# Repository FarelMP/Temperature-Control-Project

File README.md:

# Temperature-Control-Project
This is the result of the assignment of the interface and microcontroller workshop course, the project aims to measure voltage, current and tempereture while controlling brightness of halogen lamp. After all measruements, the data will visualize through node red using serial communication.

Contain included:
- Schematic and PCB layout (EAGLE).
- Node red JSON source file.
- STM32G431RBTX program for sensor reading and measurement.

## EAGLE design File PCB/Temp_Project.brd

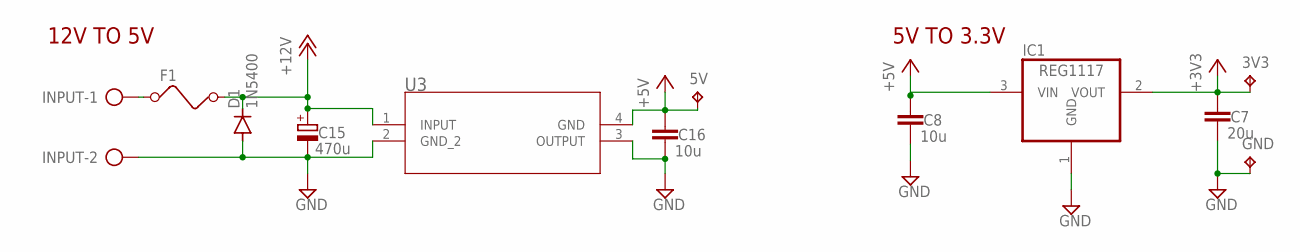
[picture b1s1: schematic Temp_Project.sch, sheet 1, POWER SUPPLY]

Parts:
3V3, 5V: TPPAD1-13; P1-13
C7: 20u; C0805
C8, C16: 10u; C0805
C15: 470u; E5-10,5
D1: 1N5400; DO201-15
F1: FUSE
GND: TPPAD1-13; P1-13
IC1: REG1117; SOT223
INPUT: AK500/2-H
U3: LM7805MPX/NOPBDCY4_TEX; DCY4_TEX

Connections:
+3V3: 3V3.TP, C7.1, IC1.2 (VOUT); also elsewhere on the board
+5V: 5V.TP, C8.1, C16.1, IC1.3 (VIN), U3.4 (GND); also elsewhere on the board
+12V: C15.+, D1.C, F1.2, U3.1 (INPUT); also elsewhere on the board
GND: C7.2, C8.2, C15.-, C16.2, D1.A, GND.TP, IC1.1 (GND), INPUT.2, U3.2 (GND_2), U3.3 (OUTPUT); also elsewhere on the board
unnamed: F1.1, INPUT.1

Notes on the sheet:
12V TO 5V
5V TO 3.3V

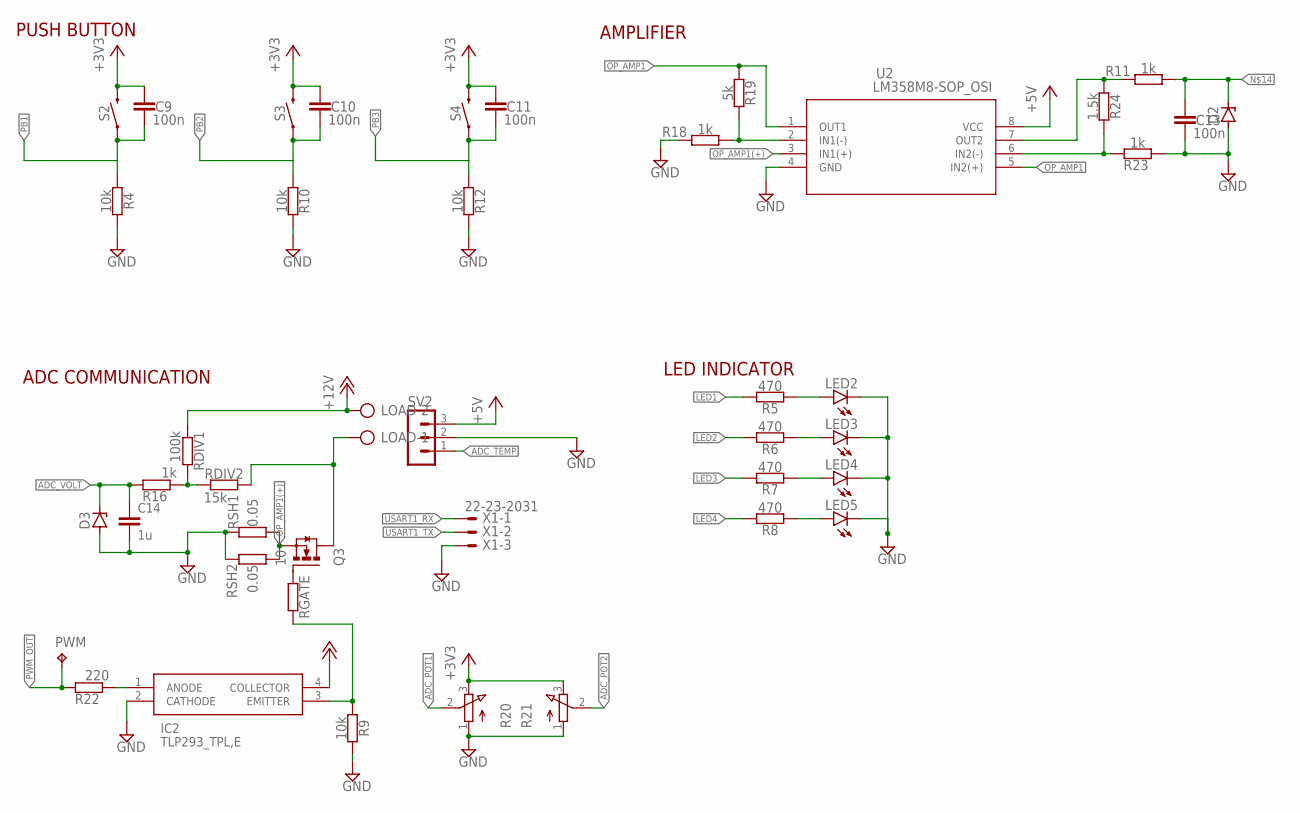
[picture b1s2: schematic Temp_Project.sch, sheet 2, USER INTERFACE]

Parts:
C9, C10, C11, C13: 100n; C0805
C14: 1u; C0805
D2, D3: ZENER 3V3; SOD80C
IC2: TLP293_TPL,E; SOIC127P700X220-4N
LED2, LED3, LED4, LED5: LED3MM
LOAD: AK500/2-H
PWM: TPPAD1-13; P1-13
Q3: IRFZ44N; SOT223
R4, R9, R10, R12: 10k; R0805
R5, R6, R7, R8: 470; R0805
R11, R16, R18, R23: 1k; R0805
R19: 5k; R0805
R20, R21: 3RP/1610N
R22: 220; R0805
R24: 1.5k; R0805
RDIV1: 100k; R0805
RDIV2: 15k; R0805
RGATE: 10; R0805
RSH1, RSH2: 0.05; 0617/22
S2, S3, S4: MOMENTARY-SWITCH-SPST-SMD-6.0X3.5MM; TACTILE_SWITCH_SMD_6.0X3.5MM
SV2: MA03-1
U2: LM358M8-SOP_OSI; 8-SOP_OSI
X1: 22-23-2031

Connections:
+3V3: C9.1, C10.1, C11.1, R20.3 (E), R21.3 (E), S2.2, S3.2, S4.2; also elsewhere on the board
+5V: SV2.3, U2.8 (VCC); also elsewhere on the board
+12V: IC2.4 (COLLECTOR), LOAD.2, RDIV1.1; also elsewhere on the board
ADC_CUR: R11.2, R24.1, U2.7 (OUT2); also elsewhere on the board
ADC_POT1: R20.2 (S); also elsewhere on the board
ADC_POT2: R21.2 (S); also elsewhere on the board
ADC_TEMP: SV2.1; also elsewhere on the board
ADC_VOLT: C14.1, D3.C, R16.2; also elsewhere on the board
GND: C13.2, C14.2, D2.A, D3.A, IC2.2 (CATHODE), LED2.K (C), LED3.K (C), LED4.K (C), LED5.K (C), R4.1, R9.1, R10.1, R12.1, R18.2, R20.1 (A), R21.1 (A), R23.1, RSH1.1, RSH2.1, SV2.2, U2.4 (GND), X1.3; also elsewhere on the board
LED1: R5.1; also elsewhere on the board
LED2: R6.1; also elsewhere on the board
LED3: R7.1; also elsewhere on the board
LED4: R8.1; also elsewhere on the board
unnamed: LED2.A, R5.2
unnamed: LED3.A, R6.2
unnamed: LED4.A, R7.2
unnamed: LED5.A, R8.2
unnamed: IC2.1 (ANODE), R22.1
unnamed: Q3.1 (G), RGATE.1
unnamed: LOAD.1, Q3.2 (D), Q3.4 (D), RDIV2.2
unnamed: IC2.3 (EMITTER), R9.2, RGATE.2
unnamed: C13.1, D2.C, R11.1
unnamed: R18.1, R19.1, U2.2 (IN1(-))
unnamed: R16.1, RDIV1.2, RDIV2.1
unnamed: R23.2, R24.2, U2.6 (IN2(-))
OP_AMP1: R19.2, U2.1 (OUT1), U2.5 (IN2(+))
OP_AMP1(+): Q3.3 (S), RSH1.2, RSH2.2, U2.3 (IN1(+))
PB1: C9.2, R4.2, S2.1; also elsewhere on the board
PB2: C10.2, R10.2, S3.1; also elsewhere on the board
PB3: C11.2, R12.2, S4.1; also elsewhere on the board
PWM_OUT: PWM.TP, R22.2; also elsewhere on the board
USART1_RX: X1.1; also elsewhere on the board
USART1_TX: X1.2; also elsewhere on the board

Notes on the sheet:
PUSH BUTTON
AMPLIFIER
ADC COMMUNICATION
LED INDICATOR

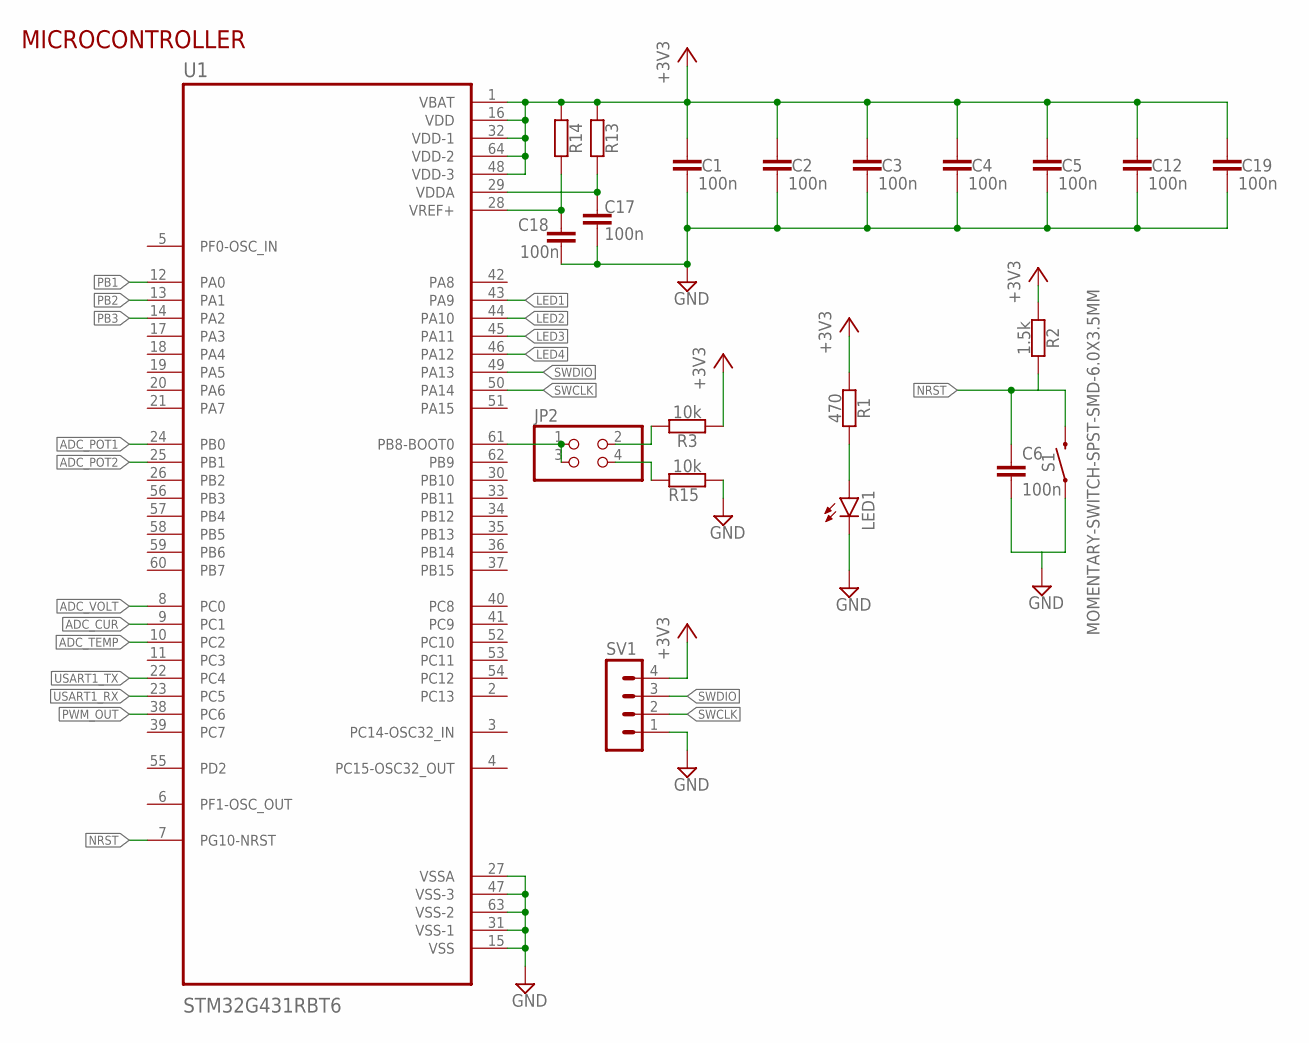
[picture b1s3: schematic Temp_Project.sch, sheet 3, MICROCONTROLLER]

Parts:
C1, C2, C3, C4, C5, C6, C12, C17, C18, C19: 100n; C0805
JP2: PINHD-2X2; 2X02
LED1: LEDCHIPLED_0805; CHIPLED_0805
R1: 470; R0805
R2: 1.5k; R0805
R3, R15: 10k; R0805
R13, R14: R-EU_R0603; R0603
S1: MOMENTARY-SWITCH-SPST-SMD-6.0X3.5MM; TACTILE_SWITCH_SMD_6.0X3.5MM
SV1: MA04-1
U1: STM32G431RBT6; QFP50P1200X1200X160-64N

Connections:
+3V3: C1.1, C2.1, C3.1, C4.1, C5.1, C12.1, C19.1, R1.1, R2.1, R3.1, R13.2, R14.2, SV1.4, U1.1 (VBAT), U1.16 (VDD), U1.32 (VDD-1), U1.48 (VDD-3), U1.64 (VDD-2); also elsewhere on the board
ADC_CUR: U1.9 (PC1); also elsewhere on the board
ADC_POT1: U1.24 (PB0); also elsewhere on the board
ADC_POT2: U1.25 (PB1); also elsewhere on the board
ADC_TEMP: U1.10 (PC2); also elsewhere on the board
ADC_VOLT: U1.8 (PC0); also elsewhere on the board
GND: C1.2, C2.2, C3.2, C4.2, C5.2, C6.2, C12.2, C17.2, C18.2, C19.2, LED1.C, R15.2, S1.1, SV1.1, U1.15 (VSS), U1.27 (VSSA), U1.31 (VSS-1), U1.47 (VSS-3), U1.63 (VSS-2); also elsewhere on the board
LED1: U1.43 (PA9); also elsewhere on the board
LED2: U1.44 (PA10); also elsewhere on the board
LED3: U1.45 (PA11); also elsewhere on the board
LED4: U1.46 (PA12); also elsewhere on the board
unnamed: LED1.A, R1.2
unnamed: JP2.1, JP2.3, U1.61 (PB8-BOOT0)
unnamed: JP2.2, R3.2
unnamed: JP2.4, R15.1
unnamed: C17.1, R13.1, U1.29 (VDDA)
unnamed: C18.1, R14.1, U1.28 (VREF+)
NRST: C6.1, R2.2, S1.2, U1.7 (PG10-NRST)
PB1: U1.12 (PA0); also elsewhere on the board
PB2: U1.13 (PA1); also elsewhere on the board
PB3: U1.14 (PA2); also elsewhere on the board
PWM_OUT: U1.38 (PC6); also elsewhere on the board
SWCLK: SV1.2, U1.50 (PA14)
SWDIO: SV1.3, U1.49 (PA13)
USART1_RX: U1.23 (PC5); also elsewhere on the board
USART1_TX: U1.22 (PC4); also elsewhere on the board

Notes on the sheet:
MICROCONTROLLER

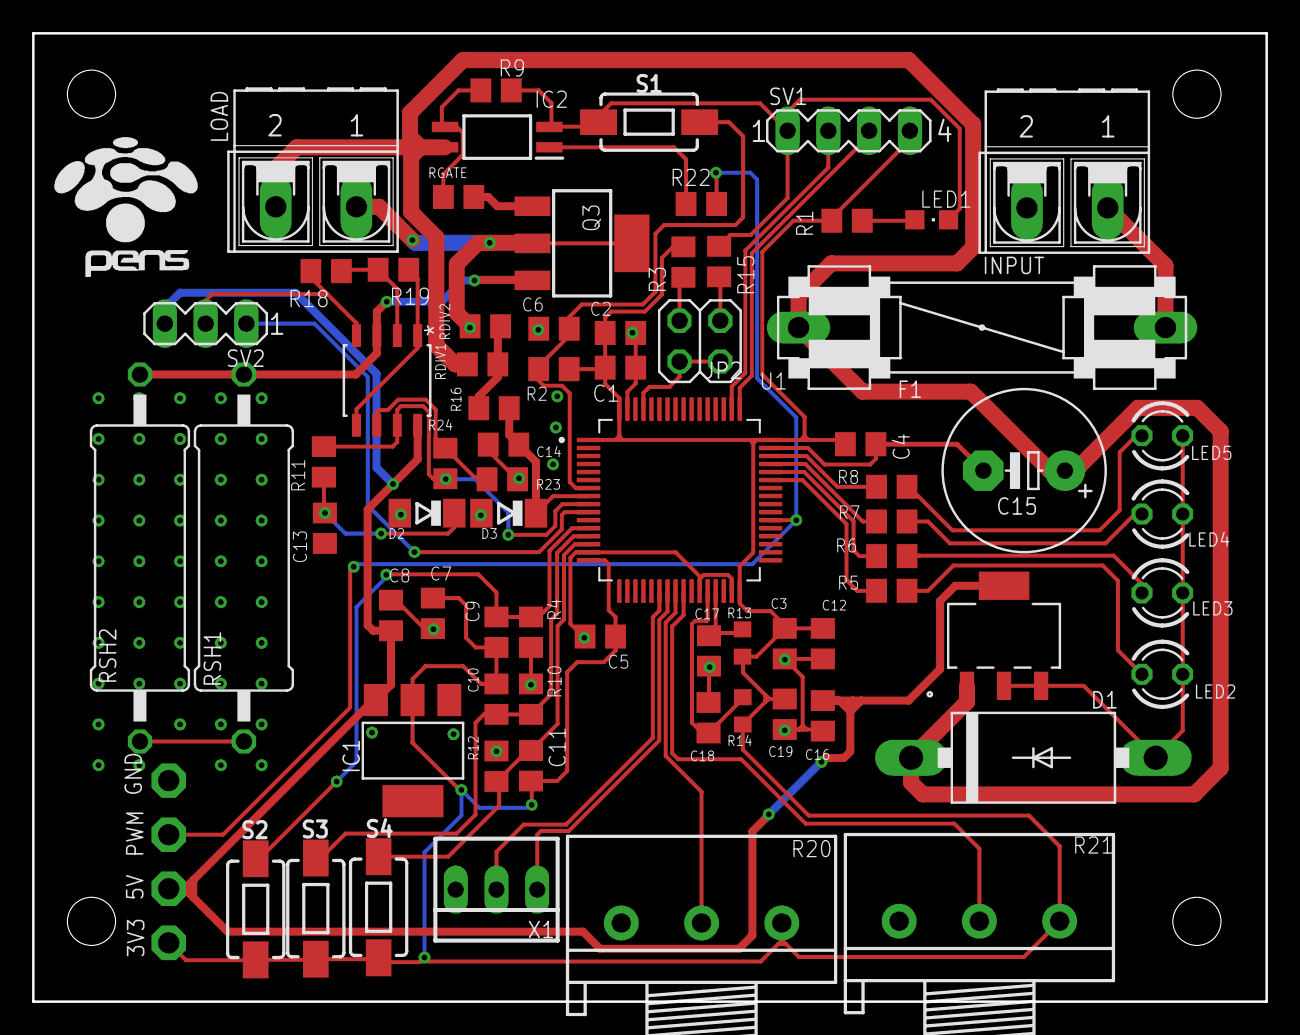
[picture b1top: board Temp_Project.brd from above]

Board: 2 copper layers, 76.8 x 60.3 mm, 76 parts (0 on the bottom side), 43 nets.

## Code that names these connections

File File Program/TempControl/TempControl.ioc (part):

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Mcu.Name=STM32G431R(6-8-B)Tx
Mcu.Package=LQFP64
Mcu.UserName=STM32G431RBTx
PA0.GPIOParameters=GPIO_Label,GPIO_ModeDefaultEXTI
PA0.GPIO_Label=PB_Mode
PA0.GPIO_ModeDefaultEXTI=GPIO_MODE_IT_RISING_FALLING
PA0.Signal=GPXTI0
PA1.GPIOParameters=GPIO_Label,GPIO_ModeDefaultEXTI
PA1.GPIO_Label=PB_StartStop
PA1.GPIO_ModeDefaultEXTI=GPIO_MODE_IT_RISING_FALLING
PA1.Signal=GPXTI1
PA10.GPIOParameters=GPIO_Label
PA10.GPIO_Label=LED_STOPRUN
PA10.Signal=GPIO_Output
PA11.GPIOParameters=GPIO_Label
PA11.GPIO_Label=LED_SETPOINT
PA11.Signal=GPIO_Output
PA12.GPIOParameters=GPIO_Label
PA12.GPIO_Label=LED
PA12.Signal=GPIO_Output
PA2.GPIOParameters=GPIO_Label,GPIO_ModeDefaultEXTI
PA2.GPIO_Label=Reset_state
PA2.GPIO_ModeDefaultEXTI=GPIO_MODE_IT_RISING_FALLING
PA2.Signal=GPXTI2
PA9.GPIOParameters=GPIO_Label
PA9.GPIO_Label=LED_MODE
PA9.Signal=GPIO_Output
PB0.GPIOParameters=GPIO_Label
PB0.GPIO_Label=POT_TIMER
PB0.Mode=IN15-Single-Ended
PB0.Signal=ADC1_IN15
PB1.GPIOParameters=GPIO_Label
PB1.GPIO_Label=POT_SETPOINT
PB1.Mode=IN12-Single-Ended
PB1.Signal=ADC1_IN12
PC0.GPIOParameters=GPIO_Label
PC0.GPIO_Label=ADC_VOLT
PC0.Mode=IN6-Single-Ended
PC0.Signal=ADC1_IN6
PC1.GPIOParameters=GPIO_Label
PC1.GPIO_Label=ADC_CUR
PC1.Mode=IN7-Single-Ended
PC1.Signal=ADC1_IN7
PC2.GPIOParameters=GPIO_Label
PC2.GPIO_Label=ADC_TEMP
PC2.Mode=IN8-Single-Ended
PC2.Signal=ADC1_IN8
PC4.Mode=Asynchronous
PC4.Signal=USART1_TX
PC5.Mode=Asynchronous
PC5.Signal=USART1_RX
PC6.GPIOParameters=GPIO_Label
PC6.GPIO_Label=PWM_GEN
PC6.Signal=S_TIM3_CH1
RCC.HSE_VALUE=8000000
RCC.SYSCLKFreq_VALUE=170000000
RCC.SYSCLKSource=RCC_SYSCLKSOURCE_PLLCLK
board=custom

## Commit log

2025-02-17 Readme Update

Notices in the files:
parts and their libraries:
SparkFun-Switches: Licensing: Creative Commons ShareAlike 4.0 International - https://creativecommons.org/licenses/by-sa/4.0
COPYRIGHT: Copyright (C) 2024 Ultra Librarian. All rights reserved.
